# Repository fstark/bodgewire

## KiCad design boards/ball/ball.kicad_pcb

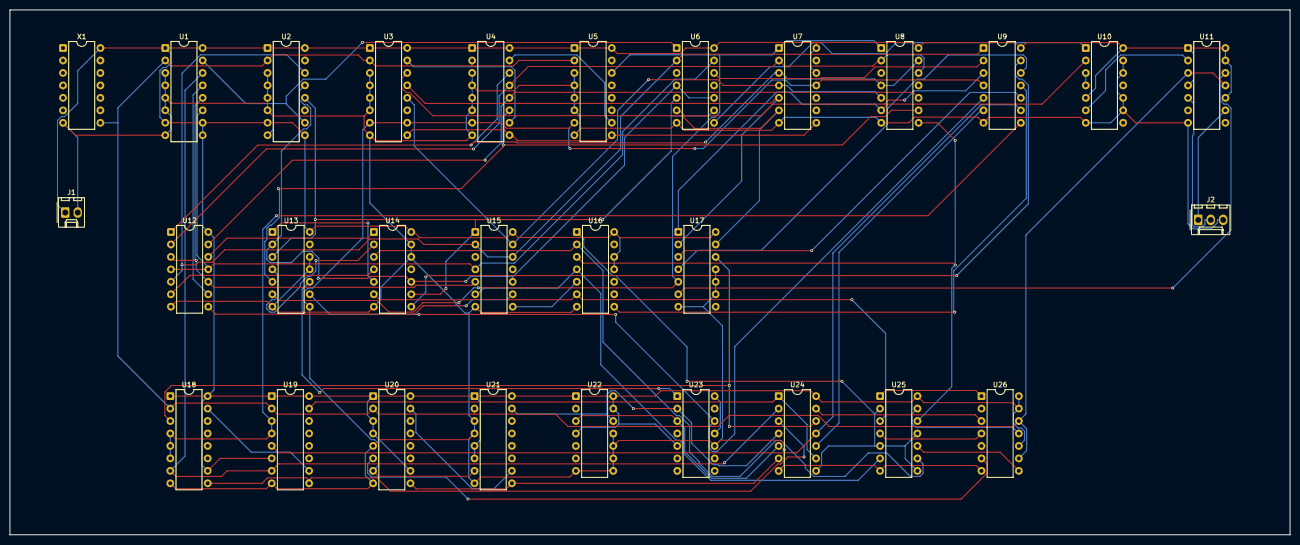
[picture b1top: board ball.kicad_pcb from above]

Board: 2 copper layers, 261.0 x 107.0 mm, 29 parts (0 on the bottom side), 67 nets.

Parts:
J1: POWER; Molex_KK-254_AE-6410-02A_1x02_P2.54mm_Vertical
J2: VIDEO; Molex_KK-254_AE-6410-03A_1x03_P2.54mm_Vertical
U1, U2, U3, U4, U5, U18, U19, U20, U21: 74LS161; DIP-16_W7.62mm
U6, U8, U15: 74LS20; DIP-14_W7.62mm
U7, U16: 74LS30; DIP-14_W7.62mm
U9: 74LS04; DIP-14_W7.62mm
U10: 74LS86; DIP-14_W7.62mm
U11: 74LS74; DIP-14_W7.62mm
U12, U17: 74LS27; DIP-14_W7.62mm
U13, U25: 74LS02; DIP-14_W7.62mm
U14, U24: 74LS00; DIP-14_W7.62mm
U22, U26: 74LS107; DIP-14_W7.62mm
U23: 74LS93; DIP-14_W7.62mm
X1: OSC; DIP-14_W7.62mm

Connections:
BALL_CK: U13.10 (3Y), U23.1 (CKB)
BALL_N: U16.1 (A), U24.8 (3Y), U25.2 (1A), U25.5 (2A), U25.8 (3A), U25.11 (4A)
BALL_OFF: U9.5 (3A), U13.9 (3B), U23.12 (QA)
BALL_QD: U23.11 (QD), U23.14 (CKA)
BHC: U18.15 (RCO), U19.10 (ENT)
BOTTOM_N: U8.8 (2Y), U16.3 (C), U25.12 (4B)
BV8: U22.3 (1Q), U23.3 (R02), U24.5 (2B)
BVC: U20.15 (RCO), U21.10 (ENT)
CLK: U1.2 (CLK), U2.2 (CLK), U3.2 (CLK), U4.2 (CLK), U5.2 (CLK), U11.3 (1CLK), U11.11 (2CLK), U18.2 (CLK), U19.2 (CLK), U20.2 (CLK), U21.2 (CLK), U26.9 (2CLK), U26.12 (1CLK), X1.8 (OUT)
FRAME_END_N: U3.9 (LOAD_N), U4.9 (LOAD_N), U5.9 (LOAD_N), U7.8 (Y)
GND: J1.2 (GND), J2.3 (GND), U1.3 (A), U1.4 (B), U1.5 (C), U1.6 (D), U1.8 (GND), U2.3 (A), U2.4 (B), U2.5 (C), U2.6 (D), U2.8 (GND), U3.3 (A), U3.4 (B), U3.5 (C), U3.6 (D), U3.8 (GND), U4.3 (A), U4.4 (B), U4.5 (C), U4.6 (D), U4.8 (GND), U5.3 (A), U5.4 (B), U5.5 (C), U5.6 (D), U5.8 (GND), U6.7 (GND), U7.7 (GND), U8.7 (GND), U9.7 (GND), U10.7 (GND), U10.9 (3A), U10.10 (3B), U10.12 (4A), U10.13 (4B), U11.7 (GND), U12.7 (GND), U13.7 (GND), U13.11 (4A), U13.12 (4B), U14.7 (GND), U14.12 (4A), U14.13 (4B), U15.7 (GND), U16.7 (GND), U17.7 (GND), U17.9 (3A), U17.10 (3B), U17.11 (3C), U18.8 (GND), U19.8 (GND), U20.5 (C), U20.8 (GND), U21.3 (A), U21.4 (B), U21.8 (GND), U22.7 (GND), U22.8 (2J), U22.9 (2CLK), U22.10 (2CLR_N), U22.11 (2K), U23.10 (GND), U24.7 (GND), U25.7 (GND), U26.7 (GND), X1.7 (GND)
H0: U1.14 (QA), U18.7 (ENP), U19.7 (ENP), U24.2 (1B)
H1: U1.13 (QB), U12.9 (3A)
H2: U1.12 (QC), U12.3 (2A), U12.10 (3B), U15.5 (1D)
H3: U1.11 (QD), U6.13 (2D), U12.4 (2B), U12.11 (3C), U15.4 (1C)
H4: U2.14 (QA), U6.2 (1B), U9.1 (1A), U12.5 (2C), U15.2 (1B), U15.12 (2C)
H4_N: U6.12 (2C), U9.2 (1Y)
H5: U2.13 (QB), U6.4 (1C), U6.10 (2B), U13.2 (1A), U14.10 (3B), U15.10 (2B)
H6: U2.12 (QC), U6.5 (1D), U6.9 (2A), U13.3 (1B), U14.9 (3A), U15.1 (1A)
H56_LOW: U13.1 (1Y), U14.5 (2B)
HBALL: U19.15 (RCO), U24.1 (1A), U24.9 (3A)
HBLANK: U9.12 (6Y), U17.4 (2B)
HBLANK_N: U9.13 (6A), U14.8 (3Y)
HC: U1.15 (RCO), U2.10 (ENT), U6.1 (1A)
HDIR: U24.13 (4B), U26.3 (1Q)
HIT_BOTTOM: U25.13 (4Y), U26.11 (2K)
HIT_LEFT: U25.1 (1Y), U26.1 (1J)
HIT_RIGHT: U25.4 (2Y), U26.4 (1K)
HIT_TOP: U25.10 (3Y), U26.8 (2J)
HLOAD_N: U18.9 (LOAD_N), U19.9 (LOAD_N), U24.3 (1Y)
HSYNC_N: U6.8 (2Y), U10.1 (1A)
LEFT_A: U12.6 (2Y), U14.4 (2A)
LEFT_N: U14.6 (2Y), U16.6 (F), U25.3 (1B)
LINE_END: U3.7 (ENP), U3.10 (ENT), U4.7 (ENP), U5.7 (ENP), U7.11 (G), U9.4 (2Y), U13.8 (3A), U20.7 (ENP), U21.7 (ENP)
LINE_END_N: U6.6 (1Y), U9.3 (2A)
MIX: U9.11 (5A), U16.8 (Y)
MIX_N: U9.10 (5Y), U17.3 (2A)
MOVE: U17.12 (1Y), U18.3 (A), U24.12 (4A)
MR: U9.8 (4Y), U18.4 (B), U18.5 (C), U18.6 (D), U19.3 (A), U19.4 (B)
MR_N: U9.9 (4A), U19.5 (C), U24.11 (4Y)
NET_A: U12.8 (3Y), U15.9 (2A)
NET_N: U15.8 (2Y), U16.5 (E)
RIGHT_N: U15.6 (1Y), U16.4 (D), U25.6 (2B)
SYNC: U10.3 (1Y), U10.4 (2A)
SYNC_N: J2.2 (SYNC_N), U11.5 (1Q)
SYNC_N_D: U10.6 (2Y), U11.2 (1D)
TOP_A: U12.12 (1Y), U14.1 (1A)
TOP_B: U13.4 (2Y), U14.2 (1B)
TOP_N: U14.3 (1Y), U16.2 (B), U25.9 (3B)
V0: U3.14 (QA), U7.6 (F), U17.13 (1C)
V1: U3.13 (QB), U7.5 (E), U17.2 (1B)
V2: U3.12 (QC), U7.4 (D), U8.5 (1D), U15.13 (2D)
V4: U4.14 (QA), U7.3 (C), U8.4 (1C), U8.13 (2D), U12.1 (1A)
V5: U4.13 (QB), U7.2 (B), U8.2 (1B), U8.12 (2C), U12.2 (1B)
V6: U4.12 (QC), U8.10 (2B), U12.13 (1C)
V7: U4.11 (QD), U8.9 (2A), U13.5 (2A)
V8: U5.14 (QA), U7.1 (A), U8.1 (1A), U13.6 (2B), U17.5 (2C)
VBALL: U9.6 (3Y), U24.10 (3B)
VC1: U3.15 (RCO), U4.10 (ENT)
VC2: U4.15 (RCO), U5.10 (ENT)
VCC: J1.1 (VCC), U1.1 (CLR_N), U1.7 (ENP), U1.9 (LOAD_N), U1.10 (ENT), U1.16 (VCC), U2.1 (CLR_N), U2.7 (ENP), U2.9 (LOAD_N), U2.16 (VCC), U3.1 (CLR_N), U3.16 (VCC), U4.1 (CLR_N), U4.16 (VCC), U5.1 (CLR_N), U5.16 (VCC), U6.14 (VCC), U7.12 (H), U7.14 (VCC), U8.14 (VCC), U9.14 (VCC), U10.5 (2B), U10.14 (VCC), U11.1 (1CLR_N), U11.4 (1PRE_N), U11.10 (2PRE_N), U11.13 (2CLR_N), U11.14 (VCC), U12.14 (VCC), U13.14 (VCC), U14.14 (VCC), U15.14 (VCC), U16.11 (G), U16.12 (H), U16.14 (VCC), U17.14 (VCC), U18.1 (CLR_N), U18.10 (ENT), U18.16 (VCC), U19.1 (CLR_N), U19.6 (D), U19.16 (VCC), U20.1 (CLR_N), U20.3 (A), U20.4 (B), U20.10 (ENT), U20.16 (VCC), U21.1 (CLR_N), U21.5 (C), U21.6 (D), U21.16 (VCC), U22.1 (1J), U22.4 (1K), U22.13 (1CLR_N), U22.14 (VCC), U23.5 (VCC), U24.14 (VCC), U25.14 (VCC), U26.10 (2CLR_N), U26.13 (1CLR_N), U26.14 (VCC), X1.14 (VCC)
VDIR_N: U20.6 (D), U26.6 (2Q_N)
VIDEO: J2.1 (VIDEO), U11.9 (2Q)
VIDEO_D: U11.12 (2D), U17.6 (2Y)
VLOAD_N: U20.9 (LOAD_N), U21.9 (LOAD_N), U24.6 (2Y)
VRCO: U21.15 (RCO), U22.12 (1CLK), U23.2 (R01), U24.4 (2A)
VSYNC_N: U8.6 (1Y), U10.2 (1B), U17.1 (1A)

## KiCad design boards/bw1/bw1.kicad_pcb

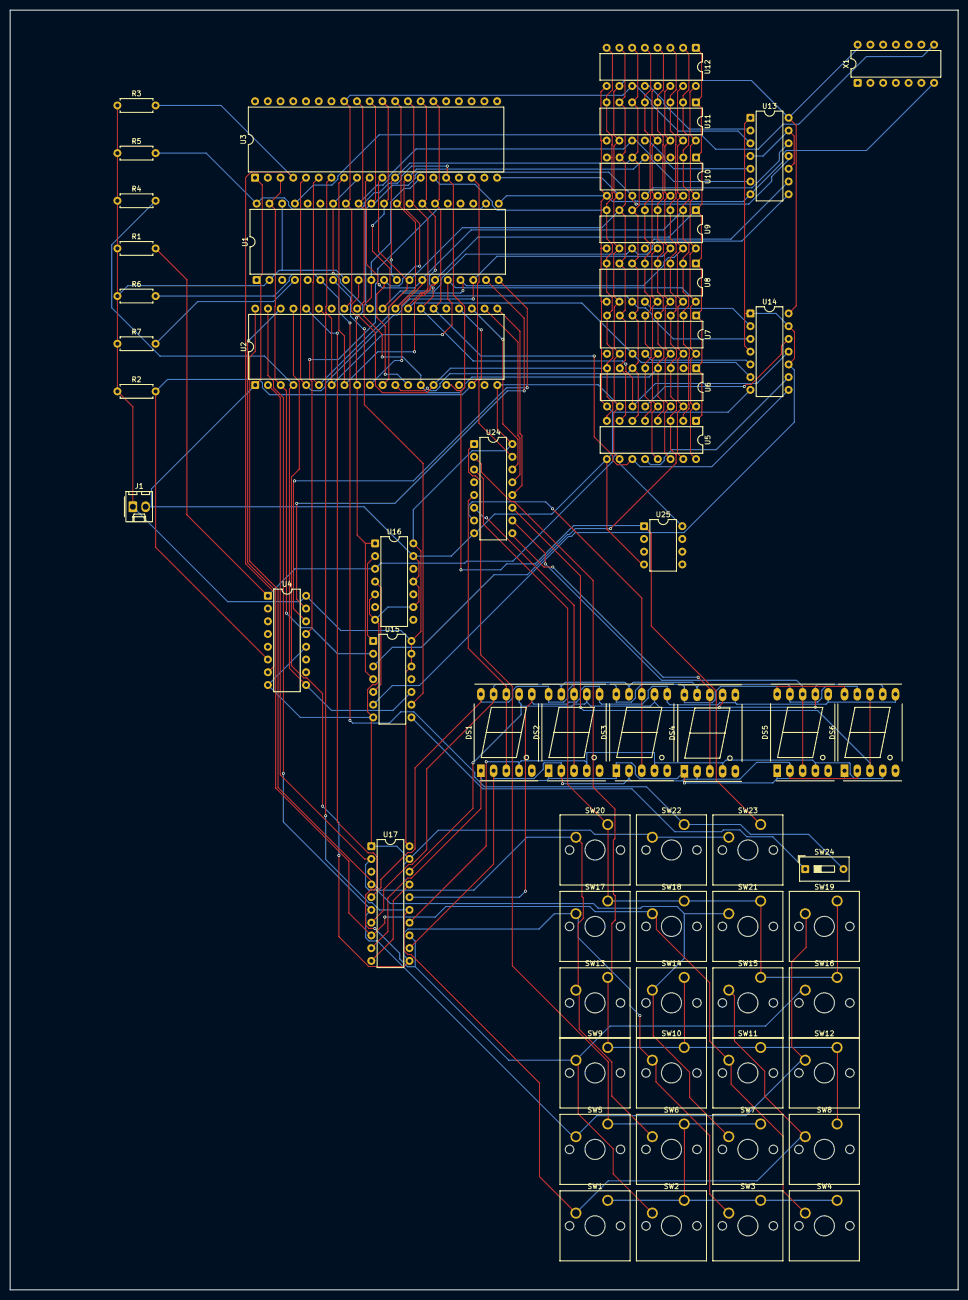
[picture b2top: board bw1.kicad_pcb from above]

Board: 2 copper layers, 189.0 x 255.1 mm, 58 parts (0 on the bottom side), 74 nets.

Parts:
DS1, DS2, DS3, DS4, DS5, DS6: DIGITCC; 7SegmentLED_LTS6760_LTS6780
J1: POWER; Molex_KK-254_AE-6410-02A_1x02_P2.54mm_Vertical
R1, R2, R3, R4, R5, R6, R7: 3k3; R_Axial_DIN0207_L6.3mm_D2.5mm_P7.62mm_Horizontal
SW1, SW2, SW3, SW4, SW5, SW6, SW7, SW8, SW9, SW10, SW11, SW12, SW13, SW14, SW15, SW16, SW17, SW18, SW19, SW20, SW21, SW22, SW23: KEY; SW_Cherry_MX_1.00u_PCB
SW24: SLIDE; SW_DIP_SPSTx01_Slide_9.78x4.72mm_W7.62mm_P2.54mm
U1: 6502; DIP-40_W15.24mm
U2, U3: 6530; DIP-40_W15.24mm
U4, U24: 74145; DIP-16_W7.62mm
U5, U6, U7, U8, U9, U10, U11, U12: 6102; DIP-16_W7.62mm
U13, U14: 74125; DIP-14_W7.62mm
U15: 74LS00; DIP-14_W7.62mm
U16: 74LS04; DIP-14_W7.62mm
U17: 74LS244; DIP-20_W7.62mm
U25: POR; DIP-8_W7.62mm
X1: OSC; DIP-14_W7.62mm

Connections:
A0: U1.9 (A0), U2.15 (A0), U3.15 (A0), U5.8 (A0), U6.8 (A0), U7.8 (A0), U8.8 (A0), U9.8 (A0), U10.8 (A0), U11.8 (A0), U12.8 (A0)
A1: U1.10 (A1), U2.14 (A1), U3.14 (A1), U5.4 (A1), U6.4 (A1), U7.4 (A1), U8.4 (A1), U9.4 (A1), U10.4 (A1), U11.4 (A1), U12.4 (A1)
A2: U1.11 (A2), U2.13 (A2), U3.13 (A2), U5.5 (A2), U6.5 (A2), U7.5 (A2), U8.5 (A2), U9.5 (A2), U10.5 (A2), U11.5 (A2), U12.5 (A2)
A3: U1.12 (A3), U2.12 (A3), U3.12 (A3), U5.6 (A3), U6.6 (A3), U7.6 (A3), U8.6 (A3), U9.6 (A3), U10.6 (A3), U11.6 (A3), U12.6 (A3)
A4: U1.13 (A4), U2.11 (A4), U3.11 (A4), U5.7 (A4), U6.7 (A4), U7.7 (A4), U8.7 (A4), U9.7 (A4), U10.7 (A4), U11.7 (A4), U12.7 (A4)
A5: U1.14 (A5), U2.10 (A5), U3.10 (A5), U5.2 (A5), U6.2 (A5), U7.2 (A5), U8.2 (A5), U9.2 (A5), U10.2 (A5), U11.2 (A5), U12.2 (A5)
A6: U1.15 (A6), U2.8 (A6), U3.8 (A6), U5.1 (A6), U6.1 (A6), U7.1 (A6), U8.1 (A6), U9.1 (A6), U10.1 (A6), U11.1 (A6), U12.1 (A6)
A7: U1.16 (A7), U2.7 (A7), U3.7 (A7), U5.16 (A7), U6.16 (A7), U7.16 (A7), U8.16 (A7), U9.16 (A7), U10.16 (A7), U11.16 (A7), U12.16 (A7)
A8: U1.17 (A8), U2.6 (A8), U3.6 (A8), U5.15 (A8), U6.15 (A8), U7.15 (A8), U8.15 (A8), U9.15 (A8), U10.15 (A8), U11.15 (A8), U12.15 (A8)
A9: U1.18 (A9), U2.5 (A9), U3.5 (A9), U5.14 (A9), U6.14 (A9), U7.14 (A9), U8.14 (A9), U9.14 (A9), U10.14 (A9), U11.14 (A9), U12.14 (A9)
A10: U1.19 (A10), U4.15 (A)
A11: U1.20 (A11), U4.14 (B)
A12: U1.22 (A12), U4.13 (C)
BUF_N: U13.1 (1OE_N), U13.4 (2OE_N), U13.10 (3OE_N), U13.13 (4OE_N), U14.1 (1OE_N), U14.4 (2OE_N), U14.10 (3OE_N), U14.13 (4OE_N), U15.6 (2Y)
D0: U1.33 (D0), U2.33 (D0), U3.33 (D0), U12.11 (DIN), U13.3 (1Y)
D1: U1.32 (D1), U2.32 (D1), U3.32 (D1), U11.11 (DIN), U13.6 (2Y)
D2: U1.31 (D2), U2.31 (D2), U3.31 (D2), U10.11 (DIN), U13.11 (4Y)
D3: U1.30 (D3), U2.30 (D3), U3.30 (D3), U9.11 (DIN), U13.8 (3Y)
D4: U1.29 (D4), U2.29 (D4), U3.29 (D4), U8.11 (DIN), U14.3 (1Y)
D5: U1.28 (D5), U2.28 (D5), U3.28 (D5), U7.11 (DIN), U14.6 (2Y)
D6: U1.27 (D6), U2.27 (D6), U3.27 (D6), U6.11 (DIN), U14.11 (4Y)
D7: U1.26 (D7), U2.26 (D7), U3.26 (D7), U5.11 (DIN), U14.8 (3Y)
DIG1: DS1.3 (CC1), DS1.8 (CC2), U24.5 (Y4_N)
DIG2: DS2.3 (CC1), DS2.8 (CC2), U24.6 (Y5_N)
DIG3: DS3.3 (CC1), DS3.8 (CC2), U24.7 (Y6_N)
DIG4: DS4.3 (CC1), DS4.8 (CC2), U24.9 (Y7_N)
DIG5: DS5.3 (CC1), DS5.8 (CC2), U24.10 (Y8_N)
DIG6: DS6.3 (CC1), DS6.8 (CC2), U24.11 (Y9_N)
DOUT0: U12.12 (DOUT), U13.2 (1A)
DOUT1: U11.12 (DOUT), U13.5 (2A)
DOUT2: U10.12 (DOUT), U13.12 (4A)
DOUT3: U9.12 (DOUT), U13.9 (3A)
DOUT4: U8.12 (DOUT), U14.2 (1A)
DOUT5: U7.12 (DOUT), U14.5 (2A)
DOUT6: U6.12 (DOUT), U14.12 (4A)
DOUT7: U5.12 (DOUT), U14.9 (3A)
GND: J1.2 (GND), SW22.2, SW23.2, U1.1 (GND), U1.21 (GND2), U2.1 (GND), U3.1 (GND), U4.8 (GND), U4.12 (D), U5.9 (GND), U6.9 (GND), U7.9 (GND), U8.9 (GND), U9.9 (GND), U10.9 (GND), U11.9 (GND), U12.9 (GND), U13.7 (GND), U14.7 (GND), U15.7 (GND), U16.5 (3A), U16.7 (GND), U16.9 (4A), U16.11 (5A), U16.13 (6A), U17.1 (1OE_N), U17.10 (GND), U17.17 (2A4), U17.19 (2OE_N), U24.8 (GND), U25.4 (GND), X1.7 (GND)
IRQ_N: R7.2, U1.4 (IRQ_N)
K0: R1.2, U4.1 (Y0_N), U5.13 (CE_N), U6.13 (CE_N), U7.13 (CE_N), U8.13 (CE_N), U9.13 (CE_N), U10.13 (CE_N), U11.13 (CE_N), U12.13 (CE_N), U16.3 (2A)
K0_N: U15.5 (2B), U16.4 (2Y)
K5: R2.2, U2.18 (CS1), U3.18 (CS1), U4.6 (Y5_N)
K6: R3.2, U3.4 (RS0), U4.7 (Y6_N)
K7: R4.2, U2.4 (RS0), U4.9 (Y7_N), U15.10 (3B)
NMI_N: R6.2, SW22.1, SW24.2, U1.6 (NMI_N)
PA0: SW7.2, SW14.2, SW21.2, U2.2 (PA0), U17.2 (1A1)
PA1: SW6.2, SW13.2, SW20.2, U2.40 (PA1), U17.4 (1A2)
PA2: SW5.2, SW12.2, SW19.2, U2.39 (PA2), U17.6 (1A3)
PA3: SW4.2, SW11.2, SW18.2, U2.38 (PA3), U17.8 (1A4)
PA4: SW3.2, SW10.2, SW17.2, U2.37 (PA4), U17.11 (2A1)
PA5: SW2.2, SW9.2, SW16.2, U2.36 (PA5), U17.13 (2A2)
PA6: SW1.2, SW8.2, SW15.2, U2.35 (PA6), U17.15 (2A3)
PB1: U2.24 (PB1), U24.15 (A)
PB2: U2.23 (PB2), U24.14 (B)
PB3: U2.22 (PB3), U24.13 (C)
PB4: U2.21 (PB4), U24.12 (D)
PHI0: U1.37 (PHI0), X1.8 (OUT)
PHI2: U1.39 (PHI2), U2.3 (PHI2), U3.3 (PHI2), U15.2 (1B)
RAM_RW: U5.3 (RW), U6.3 (RW), U7.3 (RW), U8.3 (RW), U9.3 (RW), U10.3 (RW), U11.3 (RW), U12.3 (RW), U15.3 (1Y)
RES_N: R5.2, SW23.1, U1.40 (RES_N), U2.16 (RES_N), U3.16 (RES_N), U25.1 (RST_N)
ROW0: SW1.1, SW2.1, SW3.1, SW4.1, SW5.1, SW6.1, SW7.1, U24.1 (Y0_N)
ROW1: SW8.1, SW9.1, SW10.1, SW11.1, SW12.1, SW13.1, SW14.1, U24.2 (Y1_N)
ROW2: SW15.1, SW16.1, SW17.1, SW18.1, SW19.1, SW20.1, SW21.1, U24.3 (Y2_N)
RW: U1.34 (RW), U2.9 (RW), U3.9 (RW), U15.4 (2A), U16.1 (1A)
RW_N: U15.1 (1A), U16.2 (1Y)
SEG_A: DS1.7 (A), DS2.7 (A), DS3.7 (A), DS4.7 (A), DS5.7 (A), DS6.7 (A), U17.18 (1Y1)
SEG_B: DS1.6 (B), DS2.6 (B), DS3.6 (B), DS4.6 (B), DS5.6 (B), DS6.6 (B), U17.16 (1Y2)
SEG_C: DS1.4 (C), DS2.4 (C), DS3.4 (C), DS4.4 (C), DS5.4 (C), DS6.4 (C), U17.14 (1Y3)
SEG_D: DS1.2 (D), DS2.2 (D), DS3.2 (D), DS4.2 (D), DS5.2 (D), DS6.2 (D), U17.12 (1Y4)
SEG_E: DS1.1 (E), DS2.1 (E), DS3.1 (E), DS4.1 (E), DS5.1 (E), DS6.1 (E), U17.9 (2Y1)
SEG_F: DS1.9 (F), DS2.9 (F), DS3.9 (F), DS4.9 (F), DS5.9 (F), DS6.9 (F), U17.7 (2Y2)
SEG_G: DS1.10 (G), DS2.10 (G), DS3.10 (G), DS4.10 (G), DS5.10 (G), DS6.10 (G), U17.5 (2Y3)
SST_N: SW24.1, U15.8 (3Y)
SYNC: U1.7 (SYNC), U15.9 (3A)
VCC: J1.1 (VCC), R1.1, R2.1, R3.1, R4.1, R5.1, R6.1, R7.1, U1.2 (RDY), U1.8 (VCC), U1.38 (SO), U2.20 (VCC), U3.20 (VCC), U4.16 (VCC), U5.10 (VCC), U6.10 (VCC), U7.10 (VCC), U8.10 (VCC), U9.10 (VCC), U10.10 (VCC), U11.10 (VCC), U12.10 (VCC), U13.14 (VCC), U14.14 (VCC), U15.12 (4A), U15.13 (4B), U15.14 (VCC), U16.14 (VCC), U17.20 (VCC), U24.16 (VCC), U25.8 (VCC), X1.14 (VCC)
